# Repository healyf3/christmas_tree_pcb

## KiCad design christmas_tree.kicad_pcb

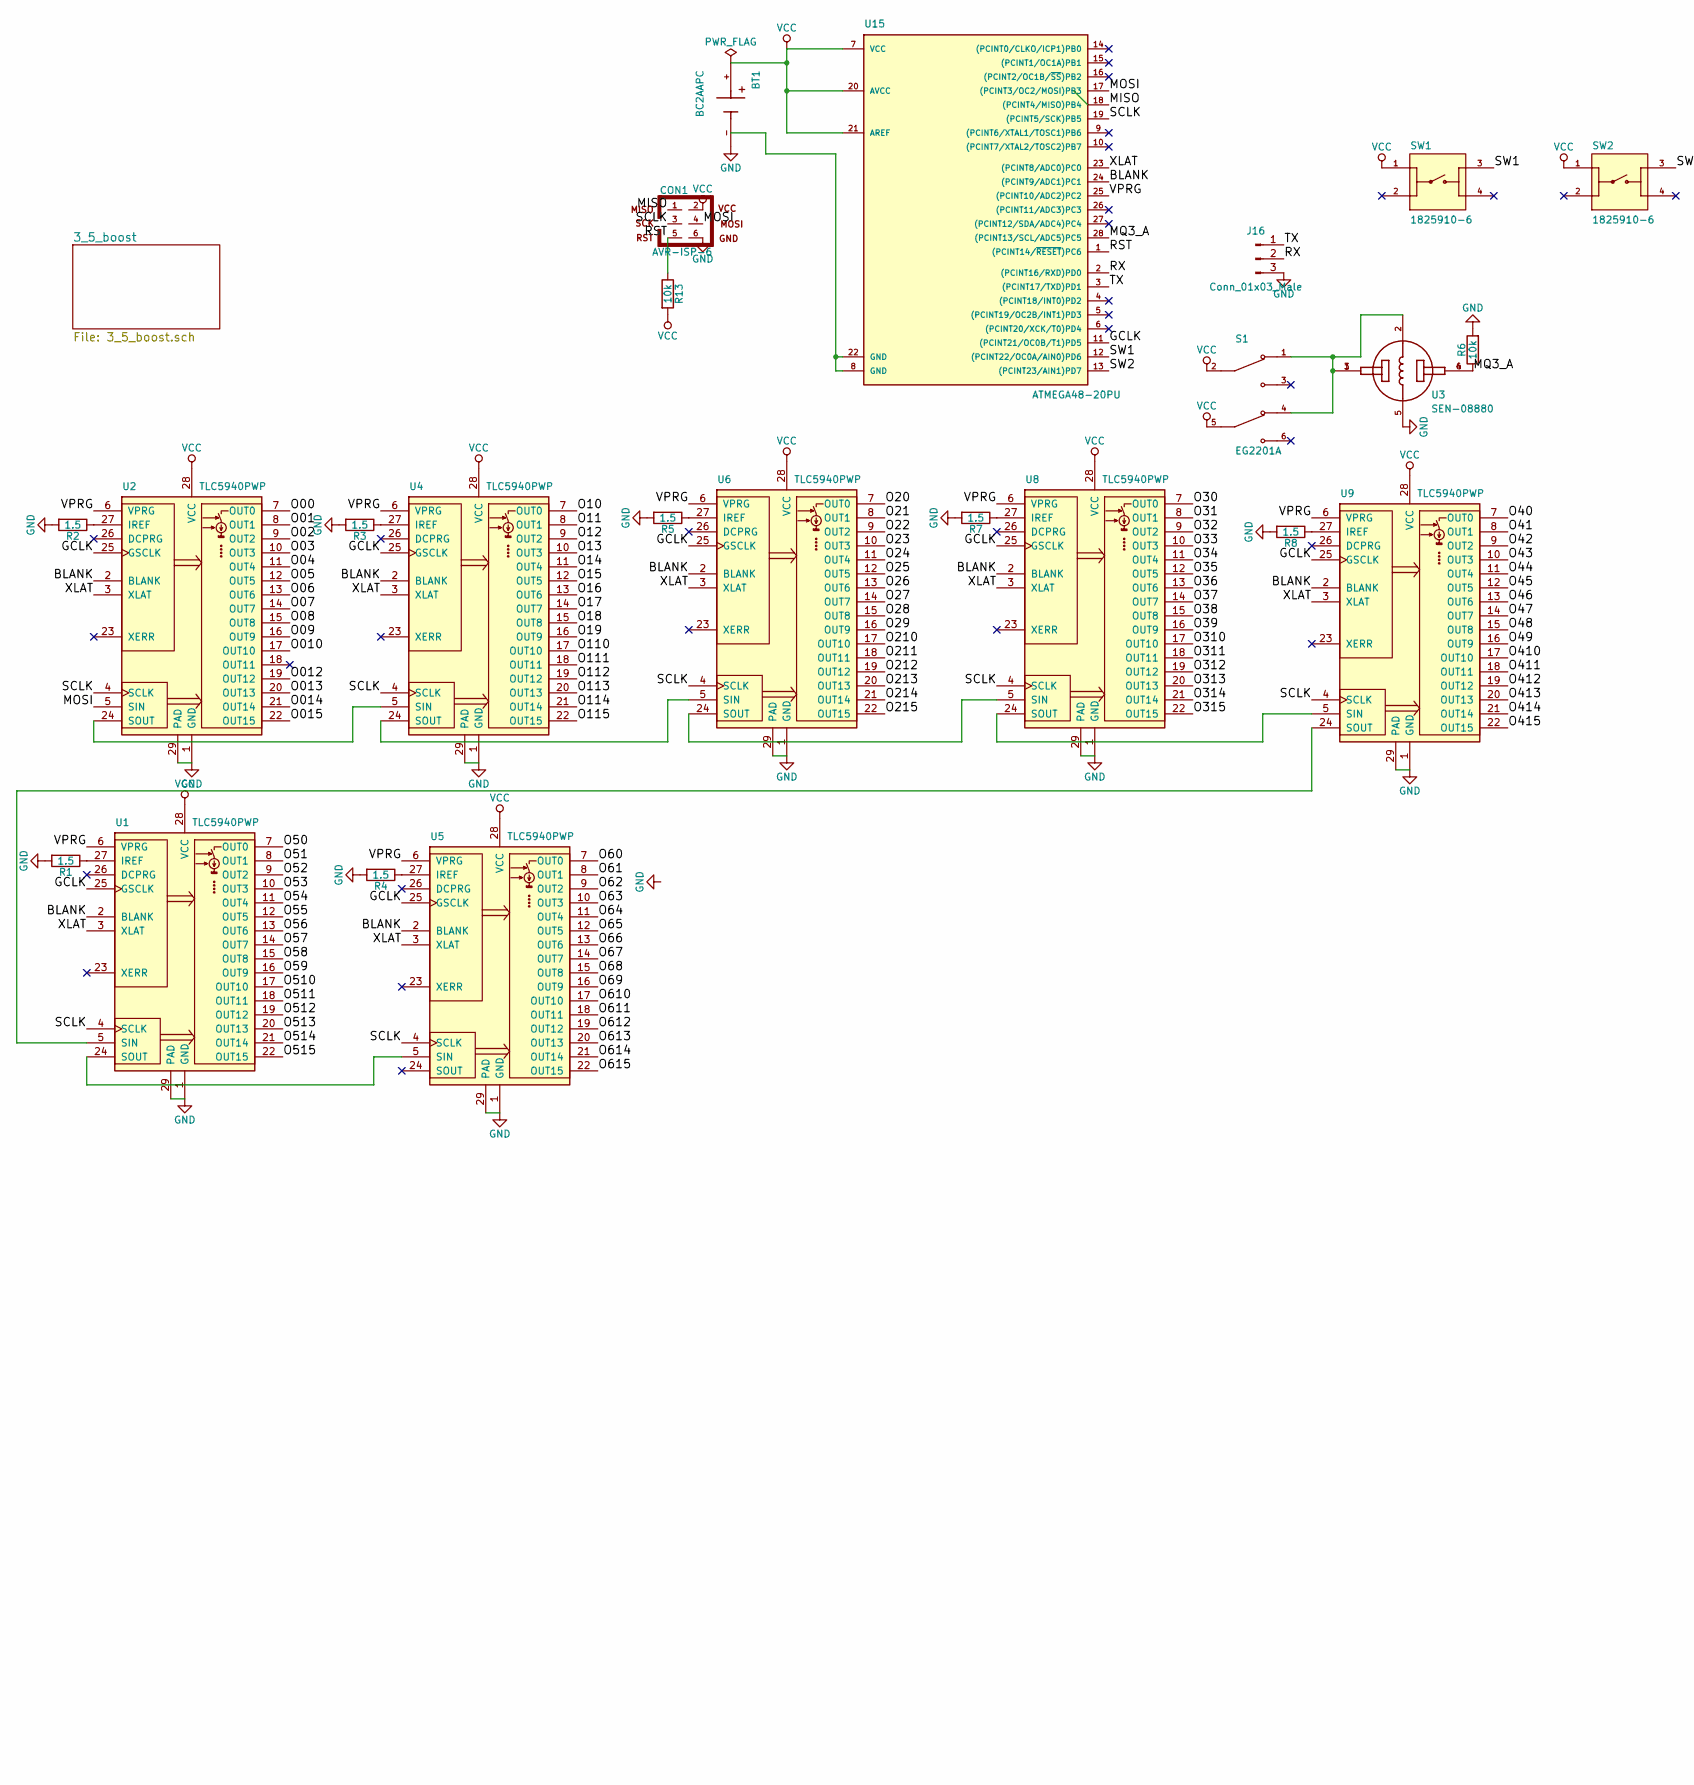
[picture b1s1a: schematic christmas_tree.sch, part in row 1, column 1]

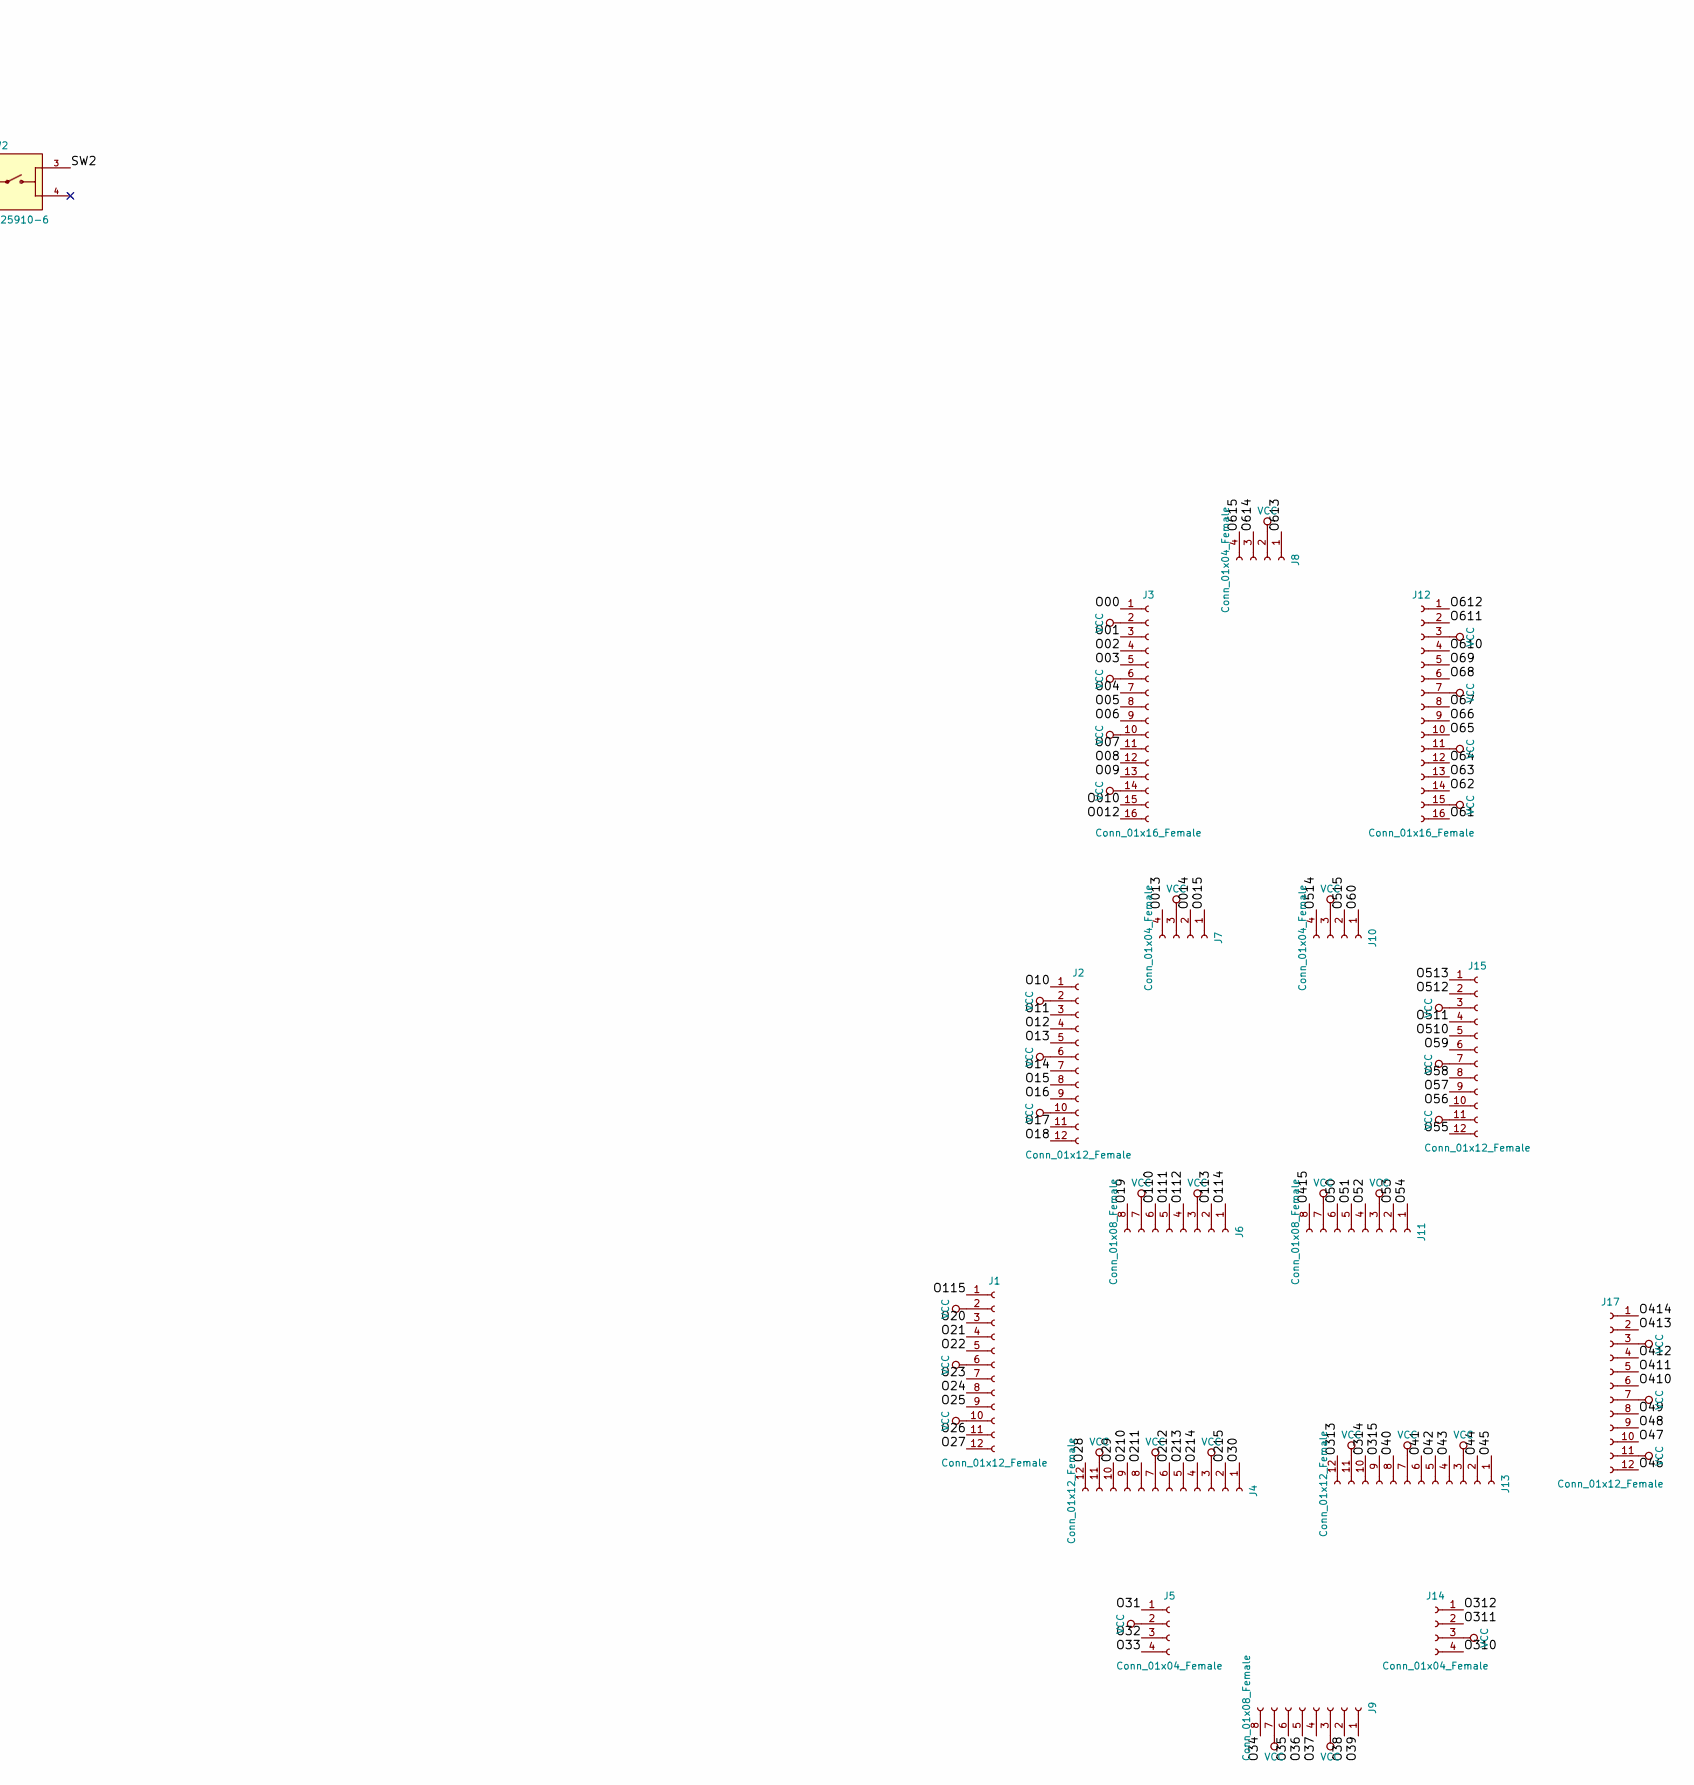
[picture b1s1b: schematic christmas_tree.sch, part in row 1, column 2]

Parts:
BT1: BC2AAPC; BAT_BC2AAPC; PARTREV M
CON1: AVR-ISP-6; Pin_Header_Straight_2x03_Pitch2.54mm
J1, J2, J4, J13, J15, J17: Conn_01x12_Female; Molex_KK-6410-12_12x2.54mm_Straight
J3, J12: Conn_01x16_Female; Molex_KK-6410-16_16x2.54mm_Straight
J5, J7, J8, J10, J14: Conn_01x04_Female; Molex_KK-6410-04_04x2.54mm_Straight
J6, J9, J11: Conn_01x08_Female; Molex_KK-6410-08_08x2.54mm_Straight
J16: Conn_01x03_Male; Molex_KK-6410-03_03x2.54mm_Straight
R1, R2, R3, R4, R5, R7, R8: 1.5; R_0603_HandSoldering
R6, R13: 10k; R_0603_HandSoldering
S1: EG2201A; SW_EG2201A; PARTREV C
SW1, SW2: 1825910-6; SW_1825910-6-4; PARTREV C10
U1, U2, U4, U5, U6, U8, U9: TLC5940PWP; HTSSOP-28_4.4x9.7mm_Pitch0.65mm_ThermalPad
U3: SEN-08880; XDCR_SEN-08880; PARTREV 1.3
U15: ATMEGA48-20PU; DIP-28_W7.62mm

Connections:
/BLANK: U1.2 (BLANK), U2.2 (BLANK), U4.2 (BLANK), U5.2 (BLANK), U6.2 (BLANK), U8.2 (BLANK), U9.2 (BLANK), U15.24 ((PCINT9/ADC1)PC1)
/GCLK: U1.25 (GSCLK), U2.25 (GSCLK), U4.25 (GSCLK), U5.25 (GSCLK), U6.25 (GSCLK), U8.25 (GSCLK), U9.25 (GSCLK), U15.11 ((PCINT21/OC0B/T1)PD5)
/MISO: CON1.1, U15.18 ((PCINT4/MISO)PB4)
/MOSI: CON1.4, U2.5 (SIN), U15.17 ((PCINT3/OC2/MOSI)PB3)
/MQ3_A: R6.1, U3.4, U3.6, U15.28 ((PCINT13/SCL/ADC5)PC5)
/O00: J3.1, U2.7 (OUT0)
/O01: J3.3, U2.8 (OUT1)
/O02: J3.4, U2.9 (OUT2)
/O03: J3.5, U2.10 (OUT3)
/O04: J3.7, U2.11 (OUT4)
/O05: J3.8, U2.12 (OUT5)
/O06: J3.9, U2.13 (OUT6)
/O07: J3.11, U2.14 (OUT7)
/O08: J3.12, U2.15 (OUT8)
/O09: J3.13, U2.16 (OUT9)
/O010: J3.15, U2.17 (OUT10)
/O10: J2.1, U4.7 (OUT0)
/O11: J2.3, U4.8 (OUT1)
/O012: J3.16, U2.19 (OUT12)
/O12: J2.4, U4.9 (OUT2)
/O013: J7.4, U2.20 (OUT13)
/O13: J2.5, U4.10 (OUT3)
/O014: J7.2, U2.21 (OUT14)
/O14: J2.7, U4.11 (OUT4)
/O015: J7.1, U2.22 (OUT15)
/O15: J2.8, U4.12 (OUT5)
/O16: J2.9, U4.13 (OUT6)
/O17: J2.11, U4.14 (OUT7)
/O18: J2.12, U4.15 (OUT8)
/O19: J6.8, U4.16 (OUT9)
/O20: J1.3, U6.7 (OUT0)
/O21: J1.4, U6.8 (OUT1)
/O22: J1.5, U6.9 (OUT2)
/O23: J1.7, U6.10 (OUT3)
/O24: J1.8, U6.11 (OUT4)
/O25: J1.9, U6.12 (OUT5)
/O26: J1.11, U6.13 (OUT6)
/O27: J1.12, U6.14 (OUT7)
/O28: J4.12, U6.15 (OUT8)
/O29: J4.10, U6.16 (OUT9)
/O30: J4.1, U8.7 (OUT0)
/O31: J5.1, U8.8 (OUT1)
/O32: J5.3, U8.9 (OUT2)
/O33: J5.4, U8.10 (OUT3)
/O34: J9.8, U8.11 (OUT4)
/O35: J9.6, U8.12 (OUT5)
/O36: J9.5, U8.13 (OUT6)
/O37: J9.4, U8.14 (OUT7)
/O38: J9.2, U8.15 (OUT8)
/O39: J9.1, U8.16 (OUT9)
/O40: J13.8, U9.7 (OUT0)
/O41: J13.6, U9.8 (OUT1)
/O42: J13.5, U9.9 (OUT2)
/O43: J13.4, U9.10 (OUT3)
/O44: J13.2, U9.11 (OUT4)
/O45: J13.1, U9.12 (OUT5)
/O46: J17.12, U9.13 (OUT6)
/O47: J17.10, U9.14 (OUT7)
/O48: J17.9, U9.15 (OUT8)
/O49: J17.8, U9.16 (OUT9)
/O50: J11.6, U1.7 (OUT0)
/O51: J11.5, U1.8 (OUT1)
/O52: J11.4, U1.9 (OUT2)
/O53: J11.2, U1.10 (OUT3)
/O54: J11.1, U1.11 (OUT4)
/O55: J15.12, U1.12 (OUT5)
/O56: J15.10, U1.13 (OUT6)
/O57: J15.9, U1.14 (OUT7)
/O58: J15.8, U1.15 (OUT8)
/O59: J15.6, U1.16 (OUT9)
/O60: J10.1, U5.7 (OUT0)
/O61: J12.16, U5.8 (OUT1)
/O62: J12.14, U5.9 (OUT2)
/O63: J12.13, U5.10 (OUT3)
/O64: J12.12, U5.11 (OUT4)
/O65: J12.10, U5.12 (OUT5)
/O66: J12.9, U5.13 (OUT6)
/O67: J12.8, U5.14 (OUT7)
/O68: J12.6, U5.15 (OUT8)
/O69: J12.5, U5.16 (OUT9)
/O110: J6.6, U4.17 (OUT10)
/O111: J6.5, U4.18 (OUT11)
/O112: J6.4, U4.19 (OUT12)
/O113: J6.2, U4.20 (OUT13)
/O114: J6.1, U4.21 (OUT14)
/O115: J1.1, U4.22 (OUT15)
/O210: J4.9, U6.17 (OUT10)
/O211: J4.8, U6.18 (OUT11)
/O212: J4.6, U6.19 (OUT12)
/O213: J4.5, U6.20 (OUT13)
/O214: J4.4, U6.21 (OUT14)
/O215: J4.2, U6.22 (OUT15)
/O310: J14.4, U8.17 (OUT10)
/O311: J14.2, U8.18 (OUT11)
/O312: J14.1, U8.19 (OUT12)
/O313: J13.12, U8.20 (OUT13)
/O314: J13.10, U8.21 (OUT14)
/O315: J13.9, U8.22 (OUT15)
/O410: J17.6, U9.17 (OUT10)
/O411: J17.5, U9.18 (OUT11)
/O412: J17.4, U9.19 (OUT12)
/O413: J17.2, U9.20 (OUT13)
/O414: J17.1, U9.21 (OUT14)
/O415: J11.8, U9.22 (OUT15)
/O510: J15.5, U1.17 (OUT10)
/O511: J15.4, U1.18 (OUT11)
/O512: J15.2, U1.19 (OUT12)
/O513: J15.1, U1.20 (OUT13)
/O514: J10.4, U1.21 (OUT14)
/O515: J10.2, U1.22 (OUT15)
/O610: J12.4, U5.17 (OUT10)
/O611: J12.2, U5.18 (OUT11)
/O612: J12.1, U5.19 (OUT12)
/O613: J8.1, U5.20 (OUT13)
/O614: J8.3, U5.21 (OUT14)
/O615: J8.4, U5.22 (OUT15)
/RST: CON1.5, R13.1, U15.1 ((PCINT14/~RESET~)PC6)
/RX: J16.2, U15.2 ((PCINT16/RXD)PD0)
/SCLK: CON1.3, U1.4 (SCLK), U2.4 (SCLK), U4.4 (SCLK), U5.4 (SCLK), U6.4 (SCLK), U8.4 (SCLK), U9.4 (SCLK), U15.19 ((PCINT5/SCK)PB5)
/SW1: SW1.3, U15.12 ((PCINT22/OC0A/AIN0)PD6)
/SW2: SW2.3, U15.13 ((PCINT23/AIN1)PD7)
/TX: J16.1, U15.3 ((PCINT17/TXD)PD1)
/VPRG: U1.6 (VPRG), U2.6 (VPRG), U4.6 (VPRG), U5.6 (VPRG), U6.6 (VPRG), U8.6 (VPRG), U9.6 (VPRG), U15.25 ((PCINT10/ADC2)PC2)
/XLAT: U1.3 (XLAT), U2.3 (XLAT), U4.3 (XLAT), U5.3 (XLAT), U6.3 (XLAT), U8.3 (XLAT), U9.3 (XLAT), U15.23 ((PCINT8/ADC0)PC0)
GND: BT1.-, CON1.6, J16.3, R1.2, R2.2, R3.2, R4.2, R5.2, R6.2, R7.2, R8.2, U1.1 (GND), U1.29 (PAD), U2.1 (GND), U2.29 (PAD), U3.5, U4.1 (GND), U4.29 (PAD), U5.1 (GND), U5.29 (PAD), U6.1 (GND), U6.29 (PAD), U8.1 (GND), U8.29 (PAD), U9.1 (GND), U9.29 (PAD)
unnamed: R1.1, U1.27 (IREF)
unnamed: R2.1, U2.27 (IREF)
unnamed: R3.1, U4.27 (IREF)
unnamed: R4.1, U5.27 (IREF)
unnamed: R5.1, U6.27 (IREF)
unnamed: R7.1, U8.27 (IREF)
unnamed: R8.1, U9.27 (IREF)
unnamed: S1.1, S1.4, U3.1, U3.2, U3.3
unnamed: U1.5 (SIN), U9.24 (SOUT)
unnamed: U1.24 (SOUT), U5.5 (SIN)
unnamed: U2.24 (SOUT), U4.5 (SIN)
unnamed: U4.24 (SOUT), U6.5 (SIN)
unnamed: U6.24 (SOUT), U8.5 (SIN)
unnamed: U8.24 (SOUT), U9.5 (SIN)
unnamed: U15.8 (GND), U15.22 (GND)
VCC: BT1.+, CON1.2, J1.2, J1.6, J1.10, J2.2, J2.6, J2.10, J3.2, J3.6, J3.10, J3.14, J4.3, J4.7, J4.11, J5.2, J6.3, J6.7, J7.3, J8.2, J9.3, J9.7, J10.3, J11.3, J11.7, J12.3, J12.7, J12.11, J12.15, J13.3, J13.7, J13.11, J14.3, J15.3, J15.7, J15.11, J17.3, J17.7, J17.11, R13.2, S1.2, S1.5, SW1.1, SW2.1, U1.28 (VCC), U2.28 (VCC), U4.28 (VCC), U5.28 (VCC), U6.28 (VCC), U8.28 (VCC), U9.28 (VCC), U15.7 (VCC), U15.20 (AVCC), U15.21 (AREF)

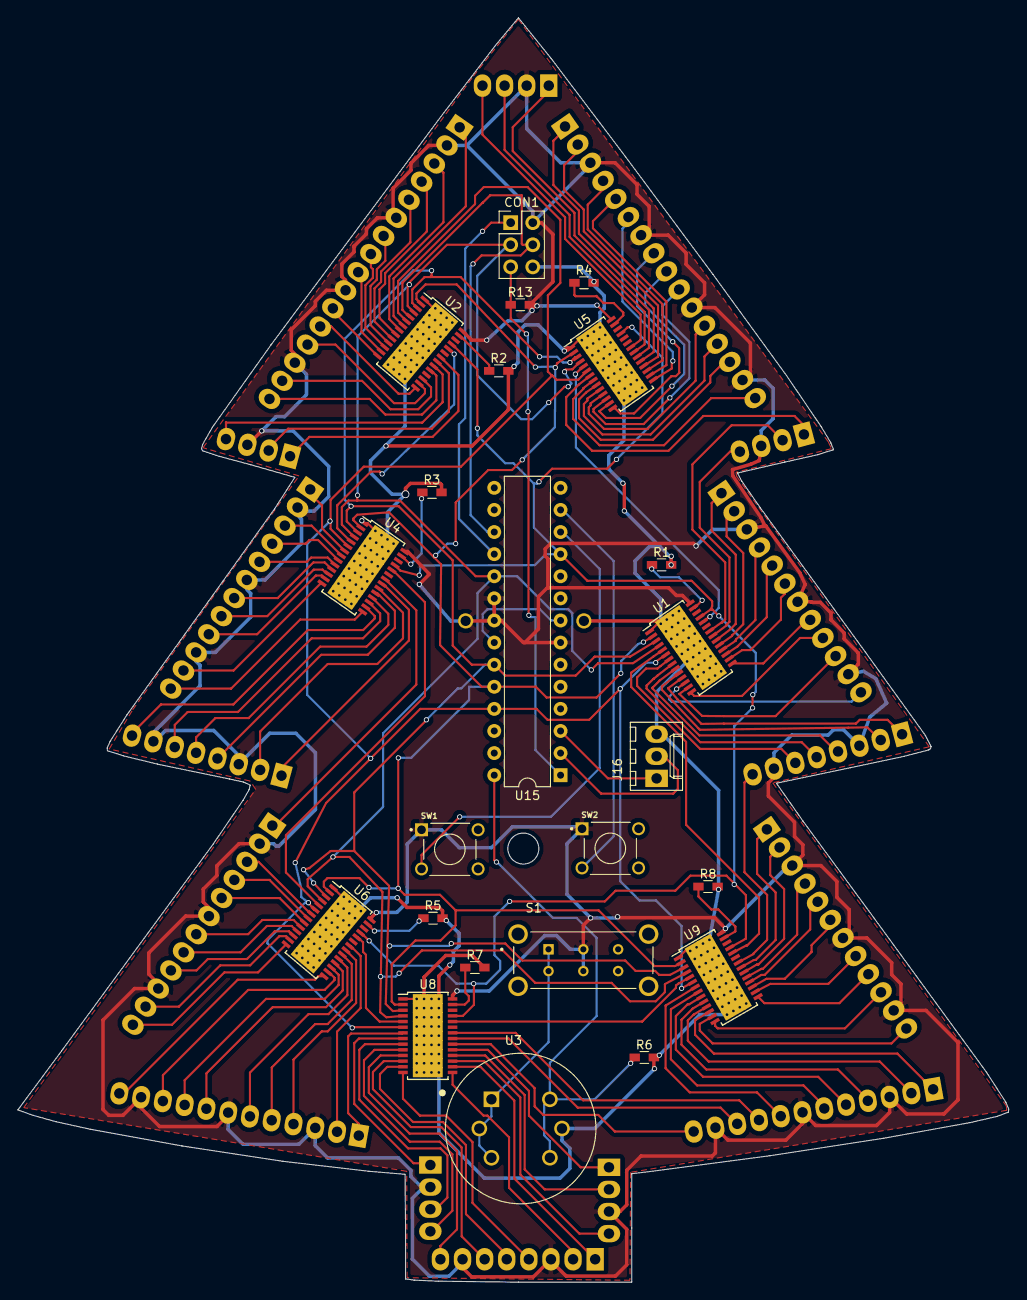
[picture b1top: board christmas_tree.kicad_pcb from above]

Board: 2 copper layers, 113.9 x 145.3 mm, 40 parts (1 on the bottom side), 141 nets.

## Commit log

2023-08-19 init
2023-09-09 Replace attiny13 with atmega48 for now
2023-10-07 Christmas tree edge cut
2023-11-19 Finish routing and generate gerber files
2023-11-30 Add bom and position documents
